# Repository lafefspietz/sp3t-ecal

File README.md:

# [sp3t-ecal](https://github.com/lafefspietz/sp3t-ecal)

Open source MEMS-based single pole three throw circuit board with improved impedance matching and SMA launches. This is in a rough draft status now, and is in active development.  This is to become a part of a system which will have two of these switch boards and a set of breakout baords for connecting the DC control lines to these RF switch boards, and to then connect to the 25 pin mirco D which is standard in most cryogenic systems used for superconducting quantum systems. Board is 50 mm square. 
 
 - [SP3TECAL.kicad_sch](SP3TECAL.kicad_sch)
 - [SP3TECAL.kicad_pcb](SP3TECAL.kicad_pcb)
 - [SP3TECAL.kicad_pro](SP3TECAL.kicad_pro)
 - [MM5230-03NDB-TR.lib](MM5230-03NDB-TR.lib)
 - [lafe_spietz_library.kicad_sym](lafe_spietz_library.kicad_sym)

## Screen shot of schematic draft:

## Screen shot of layout draft:

## Screen shot of 3d:

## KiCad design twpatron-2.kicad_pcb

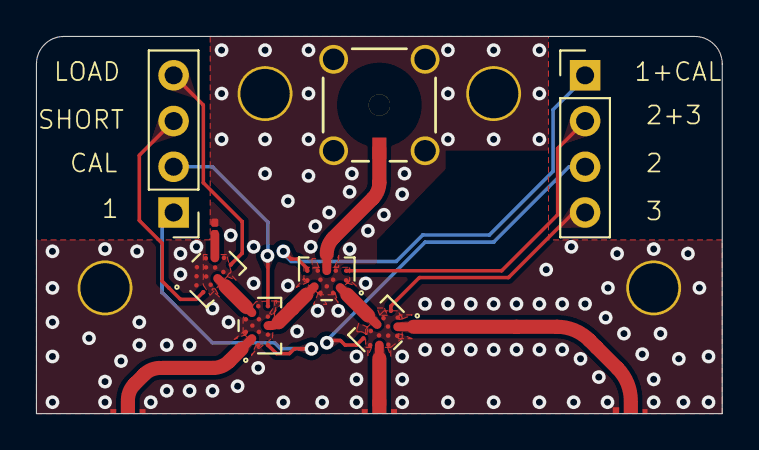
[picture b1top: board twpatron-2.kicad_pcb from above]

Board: 2 copper layers, 38.1 x 21.0 mm, 8 parts (0 on the bottom side), 14 nets.

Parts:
J1, J6: Conn_01x04; PinHeader_1x04_P2.54mm_Vertical
J3: SMP-straight-19S141-40ML5; jaws-molex-CONN_73415-3310_MOL
R1: R_US; R_0201_0603Metric
U1, U2, U3, U4: MM5800

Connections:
GND: J3.2, J3.3, J3.4, J3.5, R1.1, U1.A2 (GND), U1.A4 (GND), U1.B1 (GND), U1.B2 (GND), U1.B3 (GND), U1.B4 (GND), U1.C2 (GND), U1.D1 (GND), U1.D2 (GND), U2.A2 (GND), U2.A4 (GND), U2.B1 (GND), U2.B2 (GND), U2.B3 (GND), U2.B4 (GND), U2.C2 (GND), U2.D1 (GND), U2.D2 (GND), U3.A2 (GND), U3.A4 (GND), U3.B1 (GND), U3.B2 (GND), U3.B3 (GND), U3.B4 (GND), U3.C2 (GND), U3.D1 (GND), U3.D2 (GND), U4.A2 (GND), U4.A4 (GND), U4.B1 (GND), U4.B2 (GND), U4.B3 (GND), U4.B4 (GND), U4.C2 (GND), U4.C3 (RF1), U4.D1 (GND), U4.D2 (GND)
unnamed: J1.1, U1.A1 (VG2)
unnamed: J1.2, U1.A5 (VG1)
unnamed: J1.3, U2.A1 (VG2)
unnamed: J1.4, U2.A5 (VG1)
unnamed: J6.1, U3.A5 (VG1)
unnamed: J6.2, U3.A1 (VG2)
unnamed: J6.3, U4.A5 (VG1)
unnamed: J6.4, U4.A1 (VG2)
unnamed: U1.C3 (RF1), U2.A3 (RFC)
unnamed: U1.C1 (RF2), U3.A3 (RFC)
unnamed: J3.1, U1.A3 (RFC)
unnamed: U3.C1 (RF2), U4.A3 (RFC)
unnamed: R1.2, U4.C1 (RF2)

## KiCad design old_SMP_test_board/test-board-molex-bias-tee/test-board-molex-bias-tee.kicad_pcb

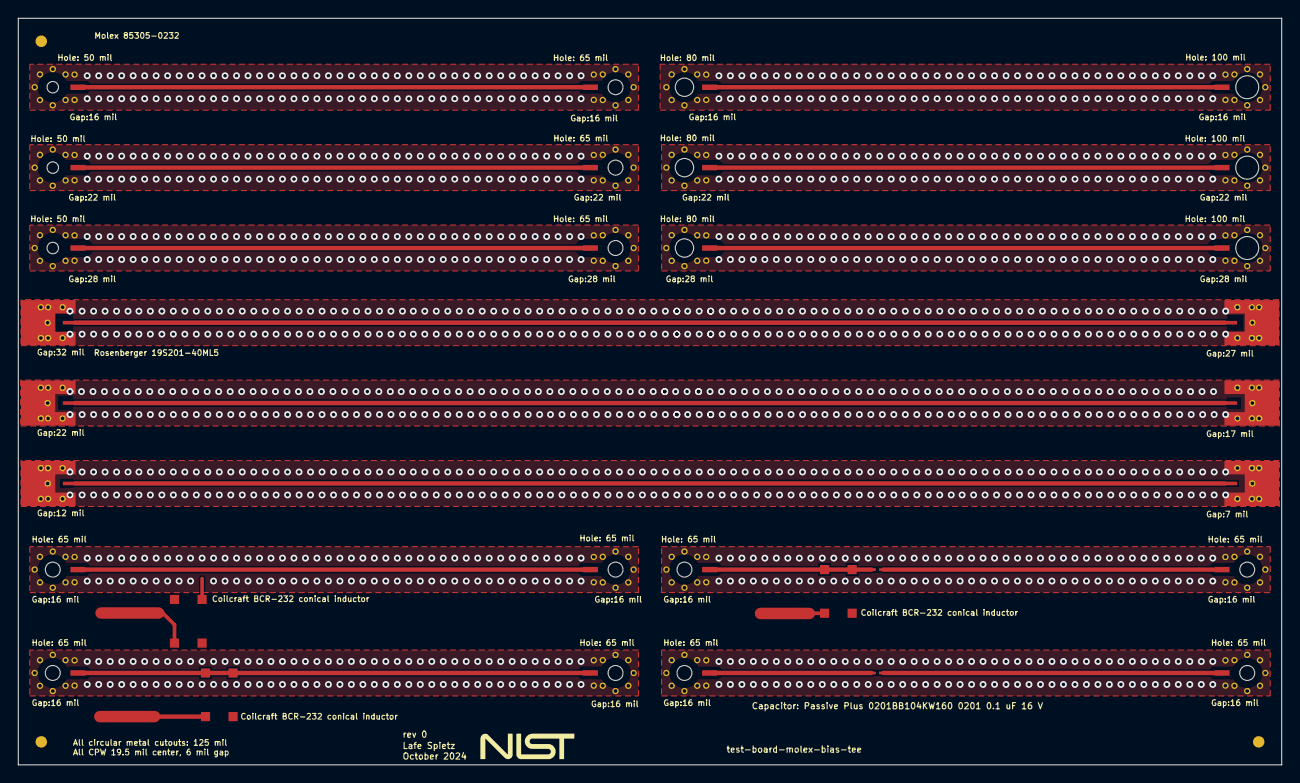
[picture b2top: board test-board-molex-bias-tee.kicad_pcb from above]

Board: 4 copper layers, 139.7 x 82.6 mm, 35 parts (0 on the bottom side), 16 nets.

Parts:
0, 0#2, 0#3: Fiducial; fiducial
C1, C2: 100 nF; 0201-capacitor
Designator4: Comment; NIST logo - TopOverlay
J1, J2, J3, J4, J5, J6, J7, J8, J9, J10, J11, J12, J25, J26, J27, J28, J29, J30, J31, J32: 85305-0232; MOLEX_85305-0232
J13, J14, J15, J16, J17, J18: SMP-right-angle-19S201-40ML5; rosenberger-19S201-40ML5
L1, L2, L3: Coilcraft BCR-232 conical inductor

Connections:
GND: J1.gnd, J2.gnd, J3.gnd, J4.gnd, J5.gnd, J6.gnd, J7.gnd, J8.gnd, J9.gnd, J10.gnd, J11.gnd, J12.gnd, J13.gnd, J14.gnd, J15.gnd, J16.gnd, J17.gnd, J18.gnd, J25.gnd, J26.gnd, J27.gnd, J28.gnd, J29.gnd, J30.gnd, J31.gnd, J32.gnd
NetC1_1: C1.1, J31.1
NetC1_2: C1.2, J32.1
NetC2_1: C2.1, J27.1, L2.1, L2.*
NetC2_2: C2.2, J28.1
NetJ1_1: J1.1, J2.1
NetJ3_1: J3.1, J4.1
NetJ5_1: J5.1, J6.1
NetJ7_1: J7.1, J8.1
NetJ9_1: J9.1, J10.1
NetJ11_1: J11.1, J12.1
NetJ13_1: J13.1, J14.1
NetJ15_1: J15.1, J16.1
NetJ17_1: J17.1, J18.1
NetJ25_1: J25.1, J26.1, L3.1
NetJ29_1: J29.1, J30.1, L1.1, L1.*

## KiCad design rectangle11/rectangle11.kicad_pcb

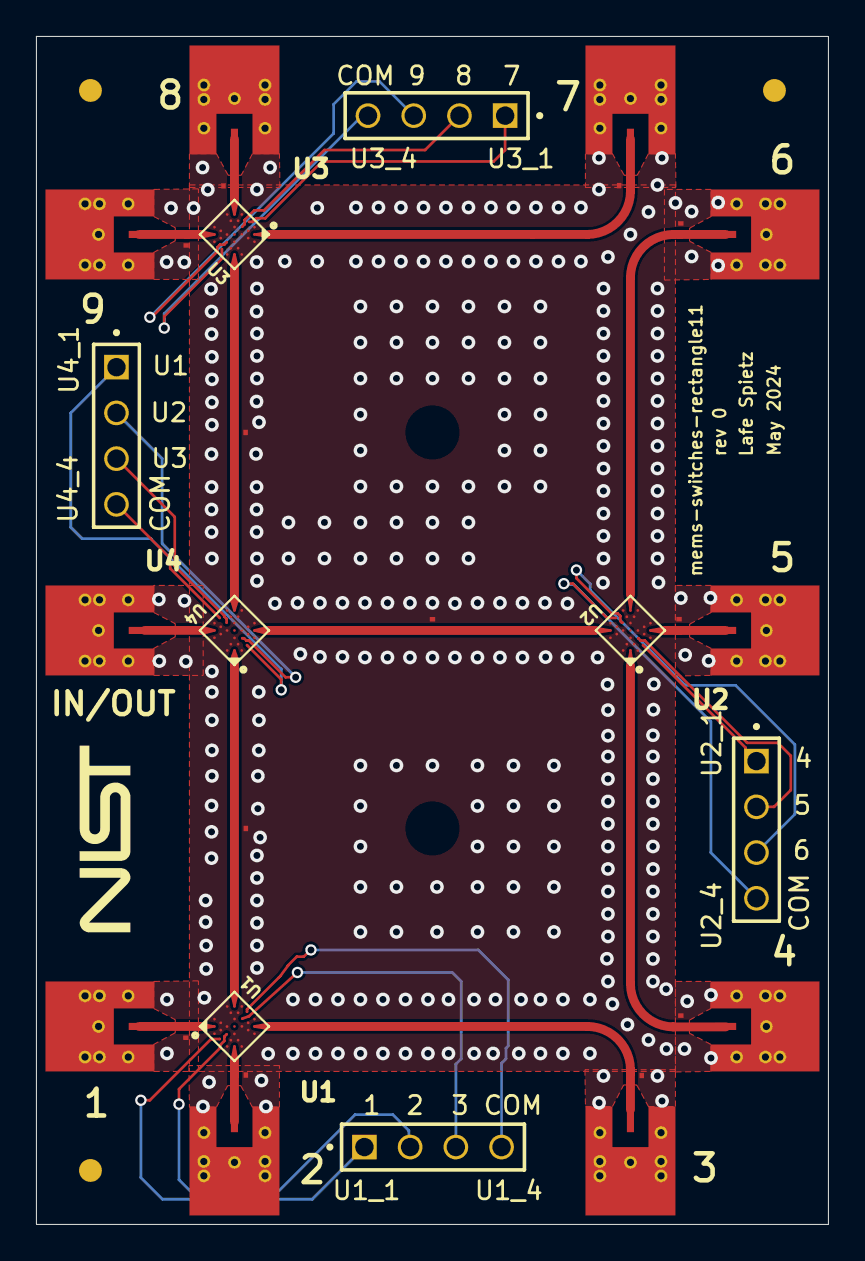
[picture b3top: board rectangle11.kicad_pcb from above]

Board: 4 copper layers, 44.0 x 66.0 mm, 32 parts (0 on the bottom side), 30 nets.

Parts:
0: Fiducial; fiducial
Designator4: Comment; NIST logo - TopOverlay
J1, J2, J3, J4, J5, J6, J7, J8, J9, J10: SMP-right-angle-19S201-40ML5; rosenberger-19S201-40ML5
J11, J12, J13, J14: TSW-104-07-G-S; SAMTEC_TSW-104-07-G-S
R1, R2, R3, R4, R5, R6, R7, R8, R9, R10, R11, R12: TE connectivity CPF0201B56K2E1; 0201-resistor
U1, U2, U3, U4: MM5130*; MM5130-NORM_PCB_NOFLOOD

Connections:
GND: J1.gnd, J2.gnd, J3.gnd, J4.gnd, J5.gnd, J6.gnd, J7.gnd, J8.gnd, J9.gnd, J10.gnd, R1.2, R2.2, R3.1, R4.1, R5.1, R6.1, R7.2, R8.2, R9.2, R10.1, R11.2, R12.2, U1.1, U1.3, U1.5, U1.6, U1.8, U1.10, U1.12, U1.13, U1.15, U1.17, U1.18, U1.19, U1.20, U1.22, U1.23, U1.24, U1.25, U1.26, U1.27, U1.28, U2.1, U2.3, U2.5, U2.6, U2.8, U2.10, U2.12, U2.13, U2.15, U2.17, U2.18, U2.19, U2.20, U2.22, U2.23, U2.24, U2.25, U2.26, U2.27, U2.28, U3.1, U3.3, U3.5, U3.6, U3.8, U3.10, U3.12, U3.13, U3.15, U3.17, U3.18, U3.19, U3.20, U3.22, U3.23, U3.24, U3.25, U3.26, U3.27, U3.28, U4.1, U4.3, U4.5, U4.6, U4.8, U4.10, U4.12, U4.13, U4.15, U4.17, U4.18, U4.19, U4.20, U4.22, U4.23, U4.24, U4.25, U4.26, U4.27, U4.28
NetJ1_1: J1.1, R1.1, U1.14
NetJ2_1: J2.1, R2.1, U1.4
NetJ3_1: J3.1, R3.2, U1.7
NetJ4_1: J4.1, R5.2, U2.14
NetJ5_1: J5.1, R6.2, U2.4
NetJ6_1: J6.1, R7.1, U2.7
NetJ7_1: J7.1, R10.2, U3.14
NetJ8_1: J8.1, R12.1, U3.4
NetJ9_1: J9.1, R11.1, U3.7
NetJ10_1: J10.1, U4.11
NetJ11_01: J11.01, U1.2
NetJ11_02: J11.02, U1.16
NetJ11_03: J11.03, U1.21
NetJ11_04: J11.04, U1.9
NetJ12_01: J12.01, U2.2
NetJ12_02: J12.02, U2.16
NetJ12_03: J12.03, U2.21
NetJ12_04: J12.04, U2.9
NetJ13_01: J13.01, U3.2
NetJ13_02: J13.02, U3.16
NetJ13_03: J13.03, U3.21
NetJ13_04: J13.04, U3.9
NetJ14_01: J14.01, U4.2
NetJ14_02: J14.02, U4.16
NetJ14_03: J14.03, U4.21
NetJ14_04: J14.04, U4.9
NetR4_2: R4.2, U1.11, U4.14
NetR8_1: R8.1, U2.11, U4.4
NetR9_1: R9.1, U3.11, U4.7

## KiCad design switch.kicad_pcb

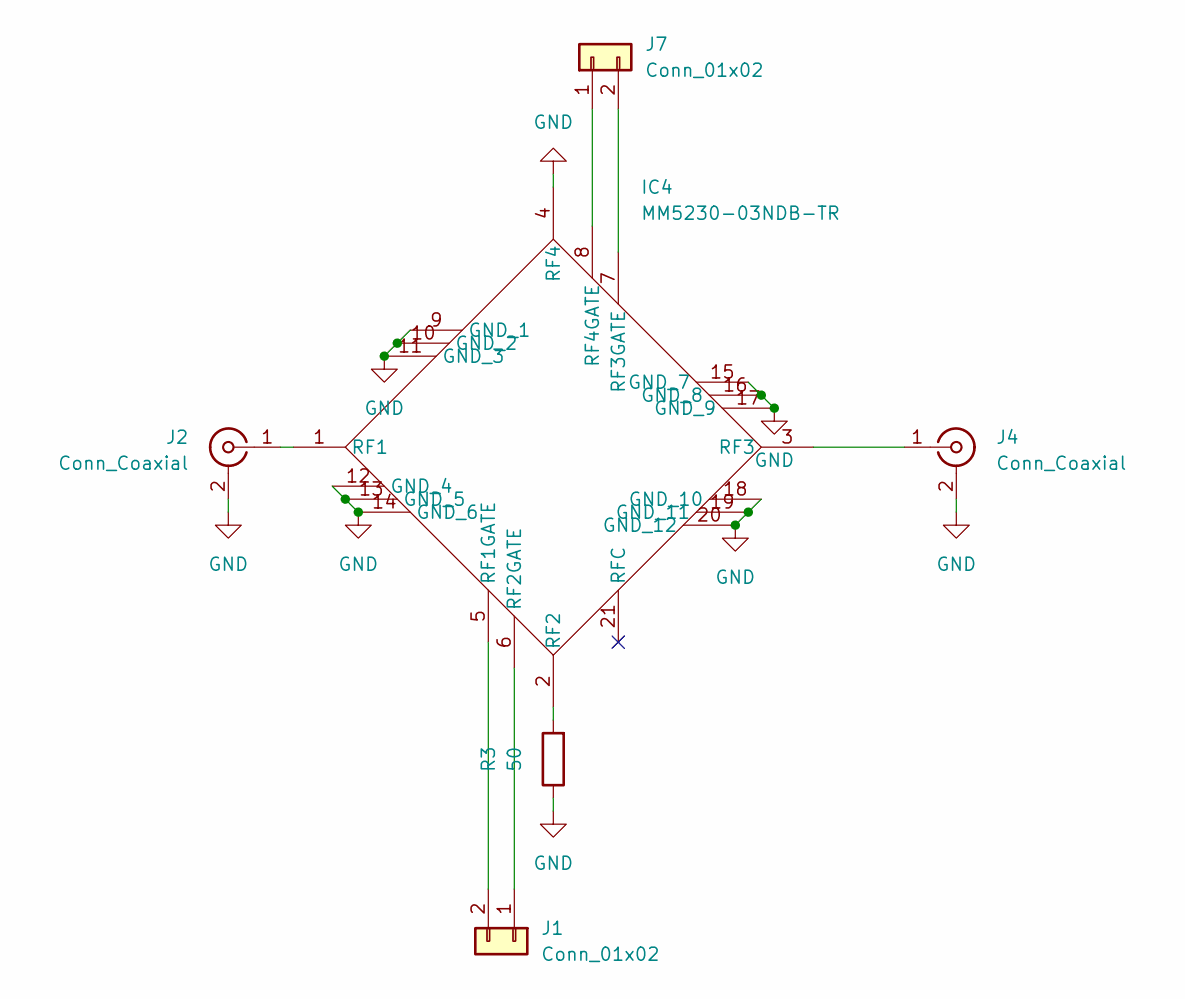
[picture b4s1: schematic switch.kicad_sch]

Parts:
IC4: MM5230-03NDB-TR; MM523003NDB; Manufacturer_Part_Number MM5230-03NDB-TR
J1, J7: Conn_01x02; PinHeader_1x02_P2.54mm_Vertical
J2, J4: Conn_Coaxial; SMA_Molex_73251-1153_EdgeMount_Horizontal
R3: 50; R_0402_1005Metric

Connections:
GND: IC4.4 (RF4), IC4.9 (GND_1), IC4.10 (GND_2), IC4.11 (GND_3), IC4.12 (GND_4), IC4.13 (GND_5), IC4.14 (GND_6), IC4.15 (GND_7), IC4.16 (GND_8), IC4.17 (GND_9), IC4.18 (GND_10), IC4.19 (GND_11), IC4.20 (GND_12), J2.2 (Ext), J4.2 (Ext), R3.1
unnamed: IC4.1 (RF1), J2.1 (In)
unnamed: IC4.5 (RF1GATE), J1.2
unnamed: IC4.2 (RF2), R3.2
unnamed: IC4.6 (RF2GATE), J1.1
unnamed: IC4.3 (RF3), J4.1 (In)
unnamed: IC4.7 (RF3GATE), J7.2
unnamed: IC4.8 (RF4GATE), J7.1

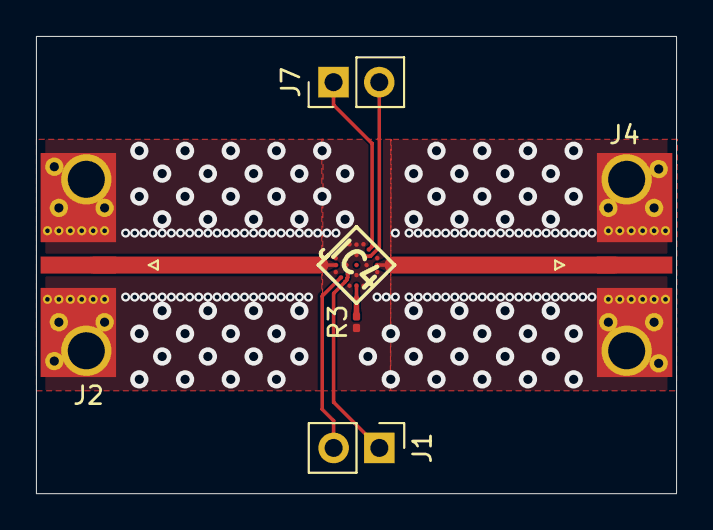
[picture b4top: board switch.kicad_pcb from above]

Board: 2 copper layers, 35.6 x 25.4 mm, 6 parts (0 on the bottom side), 8 nets.

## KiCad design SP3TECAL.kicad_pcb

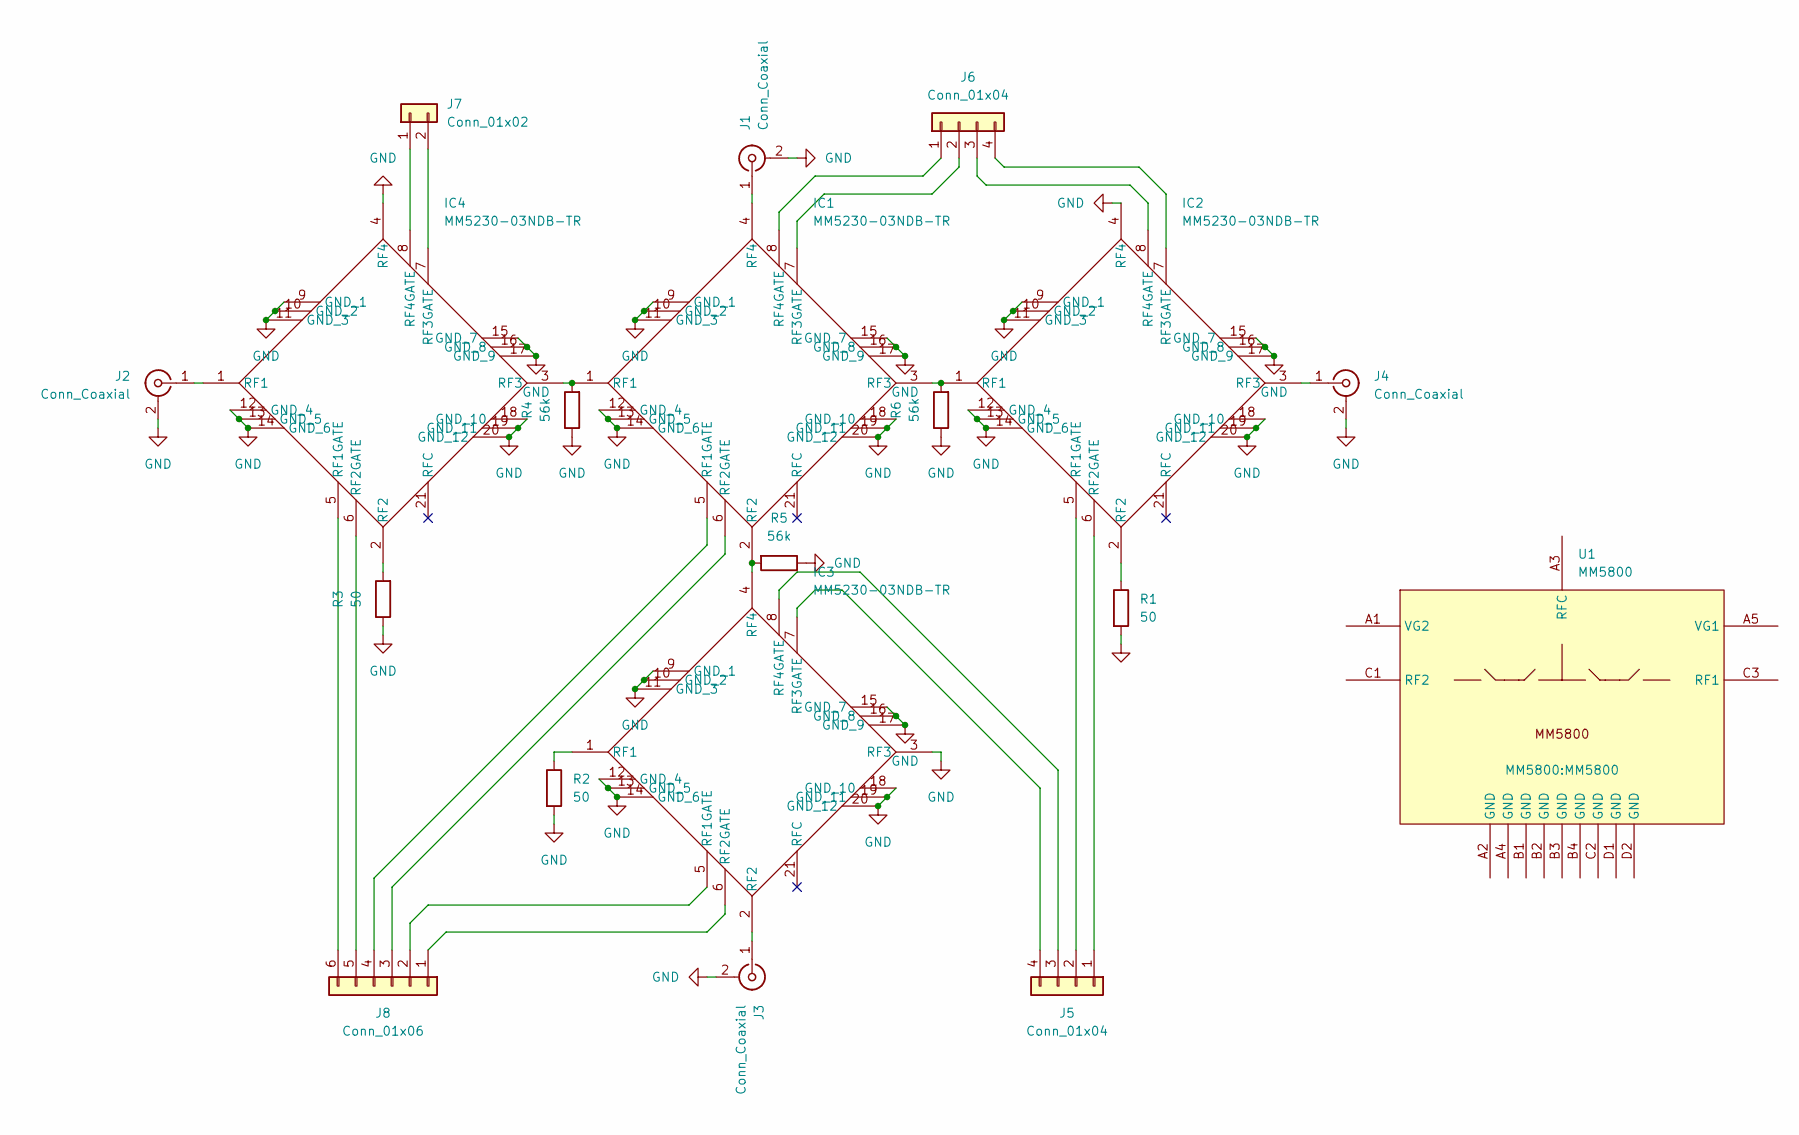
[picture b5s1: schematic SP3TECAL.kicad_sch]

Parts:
IC1, IC2, IC3, IC4: MM5230-03NDB-TR; MM523003NDB; Manufacturer_Part_Number MM5230-03NDB-TR
J1, J2, J3, J4: Conn_Coaxial; SMA_Molex_73251-1153_EdgeMount_Horizontal
J5, J6: Conn_01x04; PinHeader_1x04_P2.54mm_Vertical
J7: Conn_01x02; PinHeader_1x02_P2.54mm_Vertical
J8: Conn_01x06; PinHeader_1x06_P2.54mm_Vertical
R1, R2, R3: 50; R_0402_1005Metric
R4, R5, R6: 56k; R_0402_1005Metric
U1: MM5800; MANUFACTURER_PART_NUMBER MM5800

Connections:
GND: IC1.9 (GND_1), IC1.10 (GND_2), IC1.11 (GND_3), IC1.12 (GND_4), IC1.13 (GND_5), IC1.14 (GND_6), IC1.15 (GND_7), IC1.16 (GND_8), IC1.17 (GND_9), IC1.18 (GND_10), IC1.19 (GND_11), IC1.20 (GND_12), IC2.4 (RF4), IC2.9 (GND_1), IC2.10 (GND_2), IC2.11 (GND_3), IC2.12 (GND_4), IC2.13 (GND_5), IC2.14 (GND_6), IC2.15 (GND_7), IC2.16 (GND_8), IC2.17 (GND_9), IC2.18 (GND_10), IC2.19 (GND_11), IC2.20 (GND_12), IC3.3 (RF3), IC3.9 (GND_1), IC3.10 (GND_2), IC3.11 (GND_3), IC3.12 (GND_4), IC3.13 (GND_5), IC3.14 (GND_6), IC3.15 (GND_7), IC3.16 (GND_8), IC3.17 (GND_9), IC3.18 (GND_10), IC3.19 (GND_11), IC3.20 (GND_12), IC4.4 (RF4), IC4.9 (GND_1), IC4.10 (GND_2), IC4.11 (GND_3), IC4.12 (GND_4), IC4.13 (GND_5), IC4.14 (GND_6), IC4.15 (GND_7), IC4.16 (GND_8), IC4.17 (GND_9), IC4.18 (GND_10), IC4.19 (GND_11), IC4.20 (GND_12), J1.2 (Ext), J2.2 (Ext), J3.2 (Ext), J4.2 (Ext), R1.2, R2.2, R3.1, R4.1, R5.1, R6.1
unnamed: IC1.1 (RF1), IC4.3 (RF3), R4.2
unnamed: IC1.5 (RF1GATE), J8.4
unnamed: IC1.2 (RF2), IC3.4 (RF4), R5.2
unnamed: IC1.6 (RF2GATE), J8.3
unnamed: IC1.3 (RF3), IC2.1 (RF1), R6.2
unnamed: IC1.7 (RF3GATE), J6.2
unnamed: IC1.4 (RF4), J1.1 (In)
unnamed: IC1.8 (RF4GATE), J6.1
unnamed: IC2.5 (RF1GATE), J5.2
unnamed: IC2.2 (RF2), R1.1
unnamed: IC2.6 (RF2GATE), J5.1
unnamed: IC2.3 (RF3), J4.1 (In)
unnamed: IC2.7 (RF3GATE), J6.4
unnamed: IC2.8 (RF4GATE), J6.3
unnamed: IC3.1 (RF1), R2.1
unnamed: IC3.5 (RF1GATE), J8.2
unnamed: IC3.2 (RF2), J3.1 (In)
unnamed: IC3.6 (RF2GATE), J8.1
unnamed: IC3.7 (RF3GATE), J5.4
unnamed: IC3.8 (RF4GATE), J5.3
unnamed: IC4.1 (RF1), J2.1 (In)
unnamed: IC4.5 (RF1GATE), J8.6
unnamed: IC4.2 (RF2), R3.2
unnamed: IC4.6 (RF2GATE), J8.5
unnamed: IC4.7 (RF3GATE), J7.2
unnamed: IC4.8 (RF4GATE), J7.1

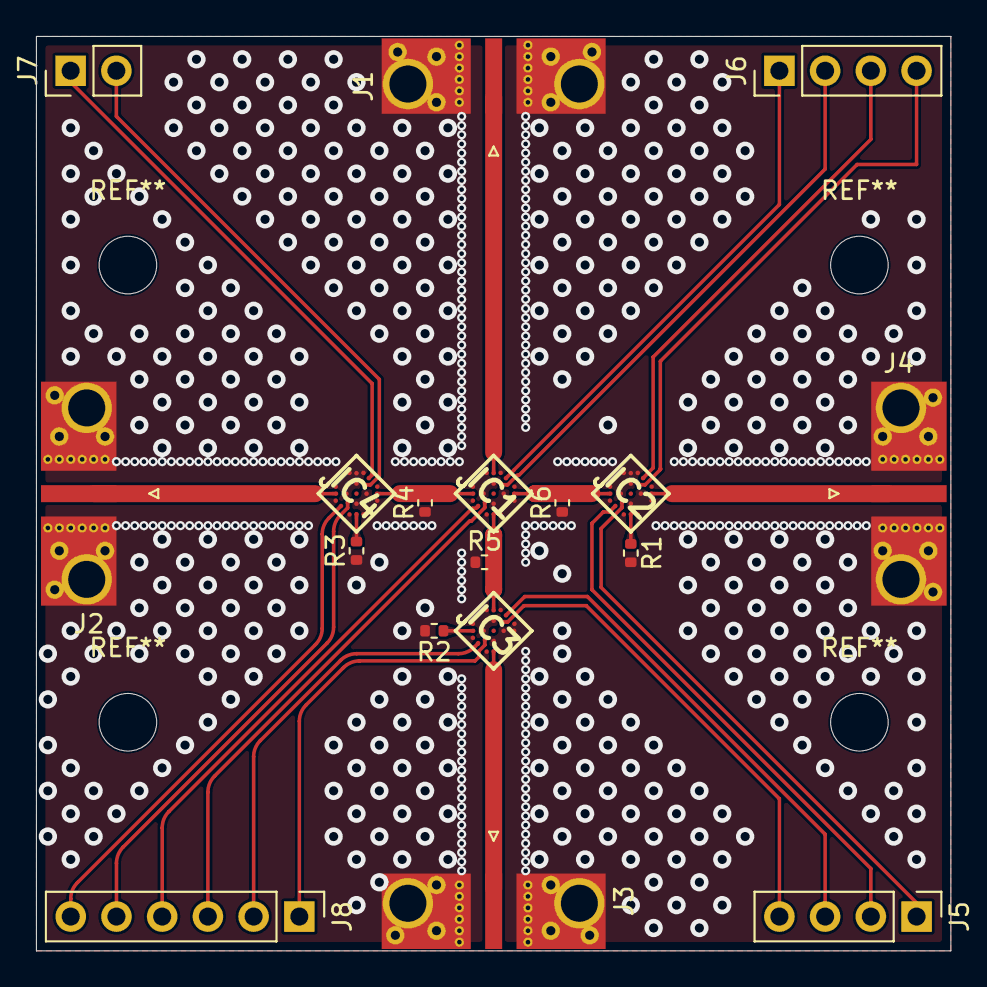
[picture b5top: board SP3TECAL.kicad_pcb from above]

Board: 2 copper layers, 50.8 x 50.8 mm, 18 parts (0 on the bottom side), 27 nets.

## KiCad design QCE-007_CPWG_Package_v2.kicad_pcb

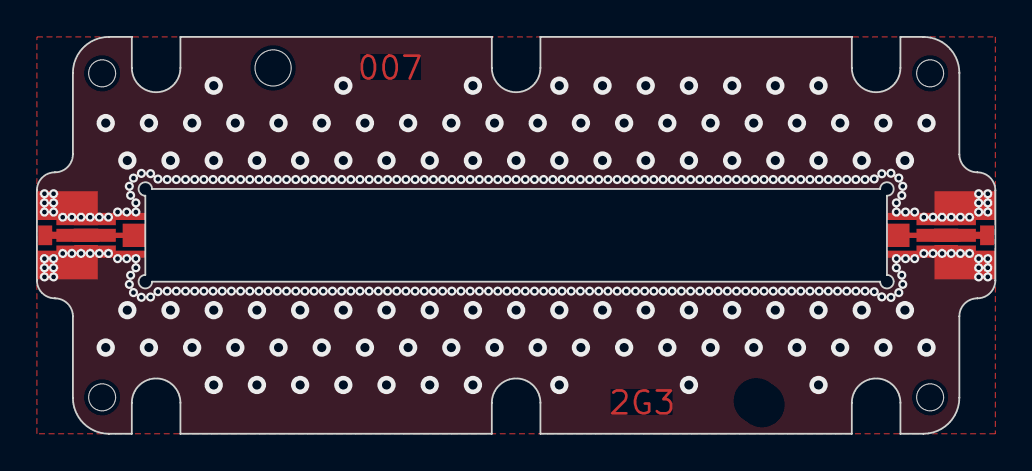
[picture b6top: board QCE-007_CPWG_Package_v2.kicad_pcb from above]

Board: 2 copper layers, 53.2 x 22.0 mm, 9 parts (0 on the bottom side), 3 nets.

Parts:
CUTOUT1: CHIP_CUTOUT
DOWEL1, DOWEL2: MOUNTING_HOLE
FID1, FID2, FID3, FID4: MOUNTING_HOLE
J1, J1#2: PANEL

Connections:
1: CUTOUT1.1, J1.1
2: CUTOUT1.2, J1#2.1
GND: CUTOUT1.2, J1.2, J1#2.2

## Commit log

2025-12-20 it's coming together!
2026-01-05 added README and README editor
2026-01-09 much progress on routing
2026-01-13 adding SOL standards and switch as DUT board
2026-01-14 small tweaks on standards boards
2026-01-15 made a southwest microwave launch and put it in the thru
2026-01-16 updated SMA launch to SW microwave on all boards
2026-03-03 used altium files to build kicad models of mm5800 and started new twpatron
2026-03-03 twpatron added to powerpoint
2026-03-04 twpa2
2026-03-05 twpatron2 close to a full draft
2026-03-06 building 3d models
2026-03-09 a full draft of pcb is essentially done now
2026-03-10 added jaws design, tweaked mechanical for M2.5 screws
2026-03-10 changed to stackup like JAWS
2026-03-11 twpatron 3d assembly coming together
2026-03-12 finished a draft of the top and bottom combination enclosure
2026-03-13 work on pcb layout, lots of small improvements and tweaks
